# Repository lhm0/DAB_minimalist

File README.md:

# Minimalist DAB+ radio for the visually impaired

## Abstract: 
An easy to use DAB+ radio for the visually impaired. The radio is configured once using an intuitive web interface. Key components of the device are an Arduino D1 R32 microprocessor board and a DABshield board for radio reception. The radio is very easy to replicate. Full documentation is available on GitHub.

<p align="center"> 

</p> 

## Part of an Accessible Devices Collection

This repository is part of a small collection of **minimalistic, accessibility-focused devices for visually impaired users**. All projects follow a similar philosophy: simple operation, tactile or acoustic feedback, and a strong focus on usability and low power consumption.

The currently available devices in this collection are:

- **[DAB+ Radio](https://github.com/lhm0/DAB_minimalist)** – This project: a minimalist, easy-to-use DAB+ radio  
- **[Talking Clock](https://github.com/lhm0/talking_clock)** – A clock that announces the time acoustically  
- **[Accessible IR Remote Control](https://github.com/lhm0/accessible_ir_remote)** – A tactile, low-power TV remote control  

All projects are designed to be practical, easy to reproduce, and suitable for everyday use by visually impaired users.

## 1. The idea
The radio was developed for a elderly visually impaired lady. The idea was to make the device as easy to use as possible. The preferred radio stations were to be selected once from the large number of DAB+ stations and assigned to 6 station buttons. In addition to these buttons, the on/off switch and the volume control should also be easy to reach with large buttons. A display has been omitted.

**Figure 1:  Minimalist DAB+ radio.** An easy to use DAB+ radio (not only) for visually impaired.

## 2. Description of the device

Digital Audio Broadcasting (DAB) is a digital radio standard being used predominatly in Europe, but also in Australia, and in parts of Africa and Asia [(Wikipedia)](https://en.wikipedia.org/wiki/Digital_Audio_Broadcasting).

The described radio is based on the DAB+ module [“DABshield”](https://www.dabshield.com), which is controlled by an Arduino microcontroller board “D1 R32”. It has the UNO form factor and can interface with UNO shields. The ESP32 microcontroller monitors 6 station buttons and the volume control. It also has a WiFi module for remote control of the radio.

The radio is housed in a 3D-printed housing (**figure 2**). All mechanical parts were designed with Fusion 360. The electronics are mounted on a carrier PCB (KiCAD). The microcontroller module and the “DABshield” are plugged on top of each other. The switches for the control of the device are also soldered onto the carrier board. This makes the radio easy and uncomplicated to replicate.

**Figure 2:  Mechnical setup of the radio.** The top cover serves as chassis of the device. All electronics components are connected through a carrier PCB.

## 3. Operation of the Device and initial setup

The user interface has been reduced to a minimum. In addition to the on/off switch and a volume control, it only consists of 6 station buttons. As the radio is intended for the visually impaired, the haptics of the controls are important.

All settings of the radio, i.e. the programming of the station buttons, the selected station and the volume, are stored in the flash memory of the microcontroller. They are immediately available when the device is switched on.

To program the station buttons in the initial setup, the device is connected to a cell phone or computer via a WiFi connection. If no connection data (SSID and password) of a WiFi network has been stored, the device switches to “Access Point Mode” when it is switched on. In this operating mode, a WiFi network with the SSID “mini_DAB” is created. You can connect to this network without using a password. The user interface is called up with a web browser by entering the address “192.168.4.1” in the address field of the browser.

**Figure 3:** The **web user interface** allows for device configuration.

The setup screen displays a scrollable list of available DAB+ radio stations. If you select an entry, the radio tunes to the station. Below the station list, the continuous text information of the selected station is displayed.

If the location of the radio has been changed, it is advisable to start a new station search. To do this, click on the corresponding button. The saved station list and the selected assignment of the station buttons will then be deleted. The new station list is automatically saved in the flash memory.

There are 6 assignable station buttons further down. These correspond to the 6 physical buttons on the radio. To assign a station to the buttons, first select it in the station list. Then click and hold on one of the station buttons. The station is then saved for this button.
The volume can also be changed via the website.

As soon as you leave the setup page, the radio works independently with the preset parameters.

## 4. Replicating the radio
All housing parts are 3D printed (**figure 4**). The design data and STL files are available in the GitHub repository. M2 and M3 nuts are inserted into some parts for the mechanical connection of the parts. To insert the nuts, the 3D print must be paused at the correct point in time (**figure5**).

**Figure 4: Mechanical parts of the Minimalist DAB+ Radio.** All parts are 3D printed.

**Figure 5: M2 and M3 nuts need to be inserted into the 3D print**

The electronic components are off-the-shelf (**figure 6**). They are listed in the parts list. The only "single source component" is the DAB+ radio module 'DABshield', developed and marketed by the UK company AVIT Research Ltd. [(50 GBP + shipping and handling).](https://www.dabshield.com/store) This module is very reliable and easy to interface with and use.

The carrier board was designed with KiCAD. The project files including the production files are available in the GitHub repository. For the prototype, the board was manufactured by JLCPCB - however, there are numerous alternatives that offer very good quality for relatively little money.

**Figure 6: The electronics components of the DAB+ Radio**

It is best to start assembling the device by fitting the carrier board. The switch, buttons and LED are mounted on the back of the board. The pin headers for connecting the DABshield and the microcontroller are positioned on the component side. The details can be found in the KiCAD design files. **Figure 7** shows the front and back of the board .

**Figure 7: Carrier PCB.** All switches and buttons are soldered to the back side, pin headers for the DABshield are on the component side.

The encoder for the volume setting is mounted on a carrier block. Note the correct position of the 5 pins of the module in the 6-pin socket (**figure 8**).

**Figure 8: Mounting of the encoder for volume control**

The two speakers are connected with a 3.5 mm jack plug. The common pole of the plug is the negative pole (**figure 9**).

**Figure 9: Two speakers are connected to a 3.5 mm jack plug**

The successive steps for assembling the appliance are shown in Figure 10. The front cover can initially be removed to allow access to the micro-USB socket of the microcontroller module. In this way, the software can be loaded onto the module.

**Figure 10: Successive steps for assembling the DAB+ radio**

## 5. Uploading the software
Although the Arduino IDE could also do the job, I prefer using Visual Studio Code with the platformIO extension. If you do not know this environment, please note, that there are numerous tutorials on Visual Studio Code and platformIO on youTube.

In order to install the software on the DAB+ radio's microcontroller, download a copy of the github repository and store it on your computer, locally. Open the sub-folder “software” in Visual Studio Code (**figure 11**). As all configuration data including the necessary libraries is included in the platformIO.ini file, no further configuration of the software is needed. Connect the Arduino R32 of the radio to your computer using a micro-USB cable. Start the compilation and the data transfer with the check button of the platformIO extension. The program will notify, when the process is completed.

**Figure 11: Visual Studio Code and platformIO**

However, the software uses a flash disk ("LittleFS"), which includes all web page data (HTML, JS, and CSS files). This data is included in the "data" subfolder of "software". In order to upload the filesystem to the controller, click on the platformIO icon (see picture, click #1) (**figure 12**). Then, click on “Build Filesystem Image” (click #2) to generate the image for the flash disk. Finally, upload the image to the microcontroller with the “Upload Filesystem Image” button (click #3). If the computer does not connect to the microcontroller, it might help to re-sart VS Code.

**Figure 12: Uploading the filesystem**

## 6. Conclusions

The minimalist DAB+ radio was developed as an easy-to-use device for the visually impaired. The complexity of the user interface, which is caused by the large variety of DAB+ stations and the wide range of functions of the standard in most devices, was deliberately avoided. A web interface was implemented for setting up the device, which enables the user to conveniently select the desired stations and assign the station buttons.

The radio uses an Arduino microcontroller. The entire software is available for further development and modification. The device is easy to replicate. All mechanical components are 3D-printed. The electronics consist of a carrier board onto which the components are soldered.

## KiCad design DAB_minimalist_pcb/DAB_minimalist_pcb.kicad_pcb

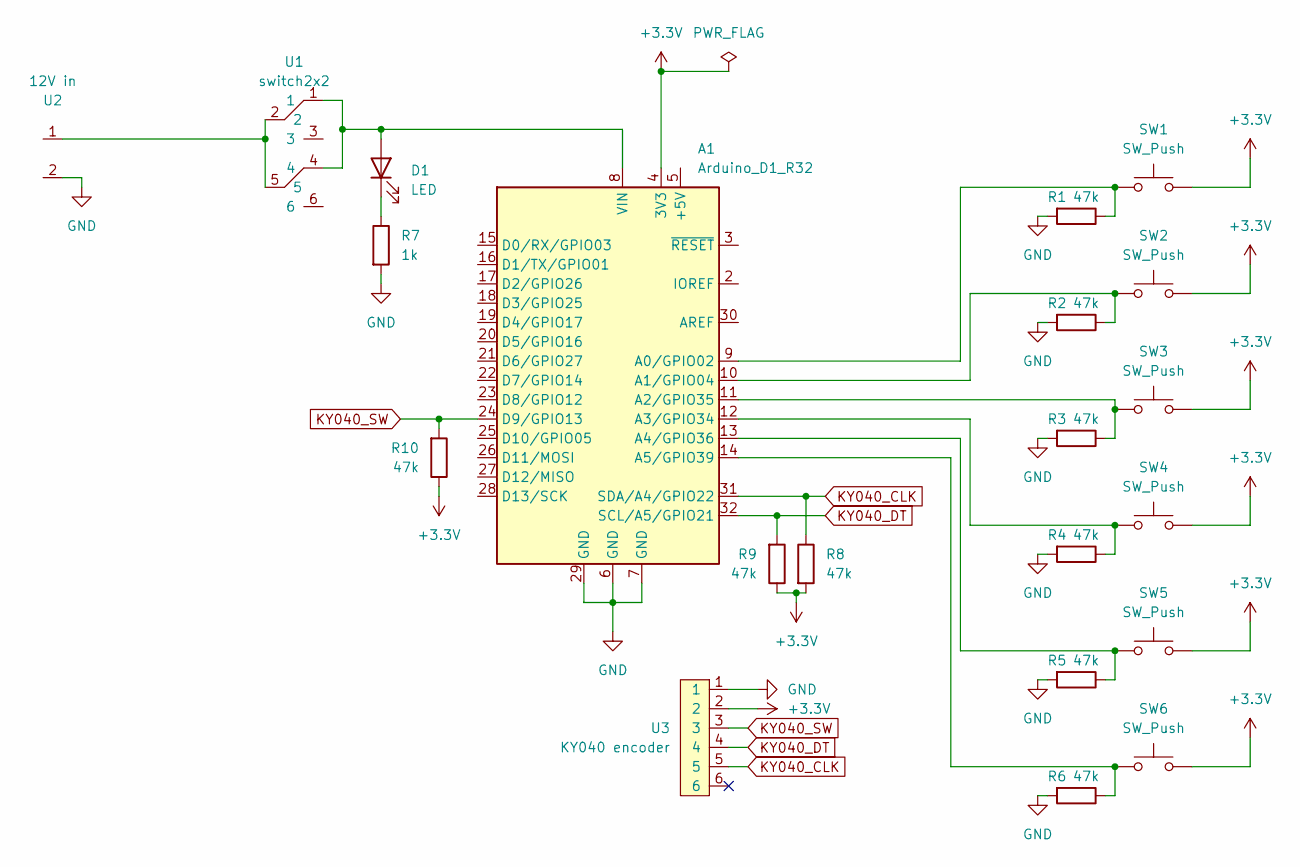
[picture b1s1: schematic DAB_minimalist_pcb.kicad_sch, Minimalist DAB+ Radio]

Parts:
A1: Arduino_D1_R32
D1: LED; LED_D3.0mm_sym
R1, R2, R3, R4, R5, R6, R8, R9, R10: 47k; R_Axial_DIN0207_L6.3mm_D2.5mm_P10.16mm_Horizontal
R7: 1k; R_Axial_DIN0207_L6.3mm_D2.5mm_P10.16mm_Horizontal
SW1, SW2, SW3, SW4, SW5, SW6: SW_Push; OmronTasterSym
U1: switch2x2; SW_Push_2x2
U2: 12V in; connector_2pin_breit
U3: KY040 encoder; connector_6pin

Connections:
+3.3V: A1.4 (3V3), R8.2, R9.1, R10.1, SW1.2, SW2.2, SW3.2, SW4.2, SW5.2, SW6.2, U3.2
GND: A1.6 (GND), A1.7 (GND), A1.29 (GND), R1.2, R2.2, R3.2, R4.2, R5.2, R6.2, R7.2, U2.2, U3.1
KY040_CLK: A1.31 (SDA/A4/GPIO22), R8.1, U3.5
KY040_DT: A1.32 (SCL/A5/GPIO21), R9.2, U3.4
KY040_SW: A1.24 (D9/GPIO13), R10.2, U3.3
unnamed: A1.9 (A0/GPIO02), R1.1, SW1.1
unnamed: A1.10 (A1/GPIO04), R2.1, SW2.1
unnamed: A1.11 (A2/GPIO35), R3.1, SW3.1
unnamed: A1.12 (A3/GPIO34), R4.1, SW4.1
unnamed: A1.13 (A4/GPIO36), R5.1, SW5.1
unnamed: A1.14 (A5/GPIO39), R6.1, SW6.1
unnamed: A1.8 (VIN), D1.2 (A), U1.1, U1.4
unnamed: D1.1 (K), R7.1
unnamed: U1.2, U1.5, U2.1

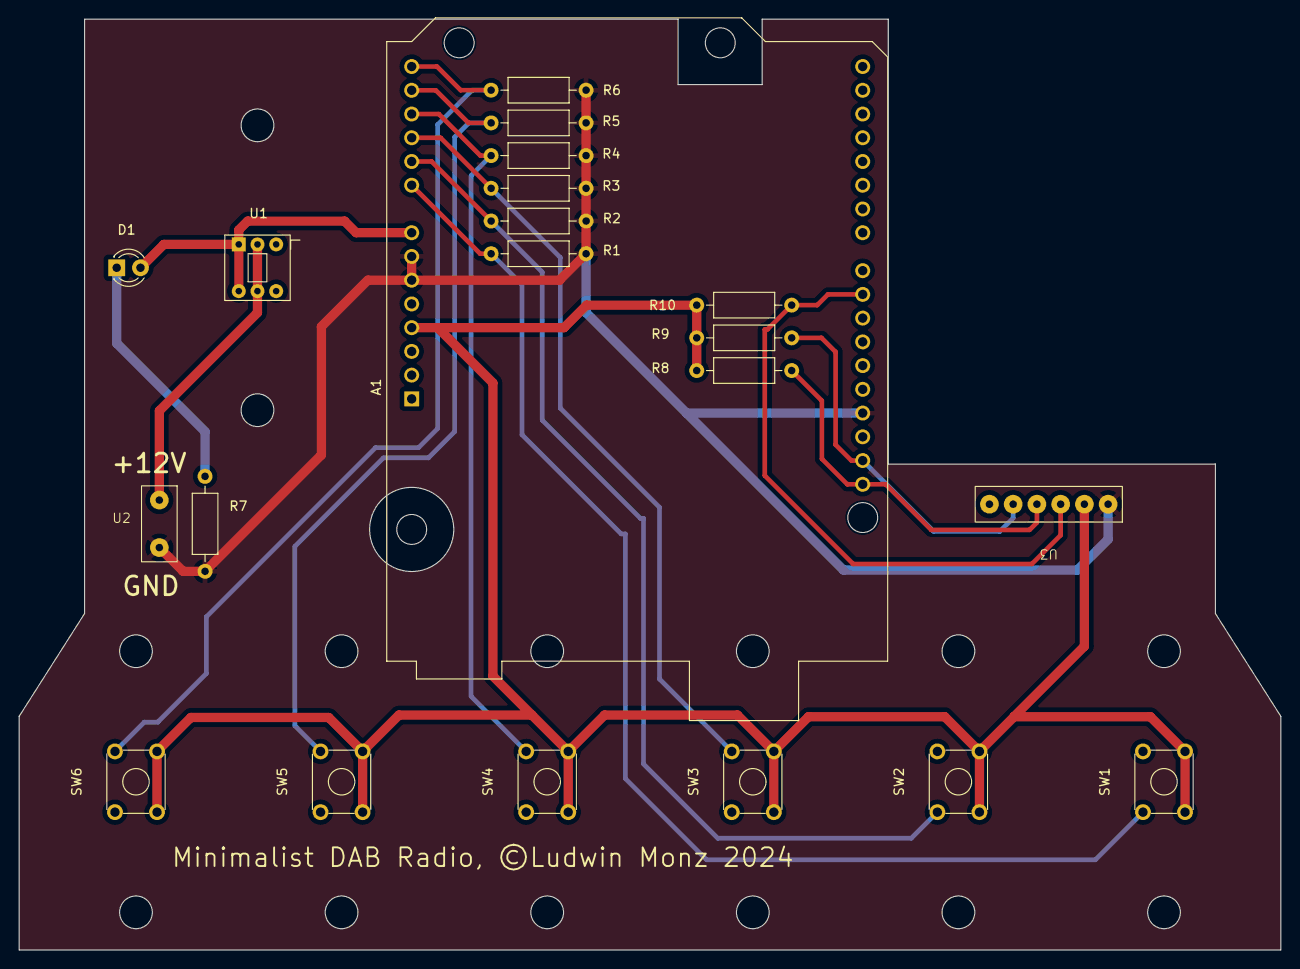
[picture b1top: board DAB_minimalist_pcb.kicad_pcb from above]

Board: 2 copper layers, 135.0 x 99.6 mm, 21 parts (0 on the bottom side), 14 nets.

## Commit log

2024-09-18 volume control fixed
2024-09-19 BOM added
2024-09-23 youtube link included
2024-09-23 readme update
2025-09-16 Remove tracked .DS_Store files and ignore them

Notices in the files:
DAB_minimalist_pcb/DAB_minimalist_pcb.kicad_pcb:
Minimalist DAB Radio, ©Ludwin Monz 2024
DAB_minimalist_pcb/DAB_minimalist_pcb.kicad_sch:
https://creativecommons.org/licenses/by-nc-sa/4.0
License: Creative Commons Attribution-Non-Commercial (CC BY-NC-SA)
